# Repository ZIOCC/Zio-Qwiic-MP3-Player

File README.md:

# Zio Qwiic MP3 Player

> This product can be available for purchase [here](https://www.smart-prototyping.com/Zio-Qwiic-MP3-Player).

#### Description

Usually, it is hard to embed sounds into a DIY project, but now we are making it much simpler, the Qwiic version Mp3 player can be very easy to set up and controlled by only writing few lines of commands. No soldering and confusing cable connecting difficulty, only tinkering fun-ness!

Just store the sound files in an Mp3 format to your SD card, plug it into the SD card slot on the module’s backside, and connect a headset/loudspeaker to the 3.5mm audio jack/terminal connector, and you are good to go!

The micro USB connector can connect to your PC and this module can turn into a micro SD card reader, which can be very useful and convenient.

##### How to play soundtracks:

To fully utilized our module, the most useful way is by using code to control everything, including which mp3 file to play, adjusting the volume, equalization, and stereo output.

Or for those of you who are lacking in the programming section, you can opt for the lazy way - give the trigger pins low input, then it will play the corresponding files, like pin #1 will play T001.mp3 file, and pin #3 will play T003.mp3 file, just like that. 

#### Specification

* Operation Voltage: 3.3V
* MP3 IC: WT2003S
* 32 levels volume controlled by code
* Supported SD Card memory: up to 32GB
* Supported File System: FAT16 and FAT32 (Doesn’t Support NTFS)
* Supported audio format: .mp3, .wav
* 3.5mm audio headphone jack
* I2C default address 0x37, can be changed by soldering jumper (the ADDR on the backside)
* I2C gateway MCU: ATTINY84A-SSU
* Dimensions: 45.9x 35.5mm
* Weight: 8.2g

#### Links

* [PCB source file and Gerber file](https://github.com/ZIOCC/Zio-Qwiic-MP3-Player)
* [Schematic](https://github.com/ZIOCC/Zio-Qwiic-MP3-Player/blob/master/Zio%20Qwiic%20MP3%20Player%20Schematic%20PDF.pdf)
* [WT2003S datasheet](https://www.smart-prototyping.com/image/data/NOA-RnD/101942%20MP3%20Player/WT2003S-16S_Chip_V1.03.pdf)
* [Demo code](https://github.com/ZIOCC/Zio-Qwiic-MP3-Player/tree/master/firmware)
* [I2C gateway firmware](https://github.com/ZIOCC/Zio-Qwiic-MP3-Player/tree/master/Gateway_MCU_Firmware)

###### About Zio
> Zio is a new line of open sourced, compact, and grid layout boards, fully integrated for Arduino and Qwiic ecosystem. Designed ideally for wearables, robotics, small-space limitations or other on the go projects. Check out other awesome Zio products [here](https://www.smart-prototyping.com/Zio).

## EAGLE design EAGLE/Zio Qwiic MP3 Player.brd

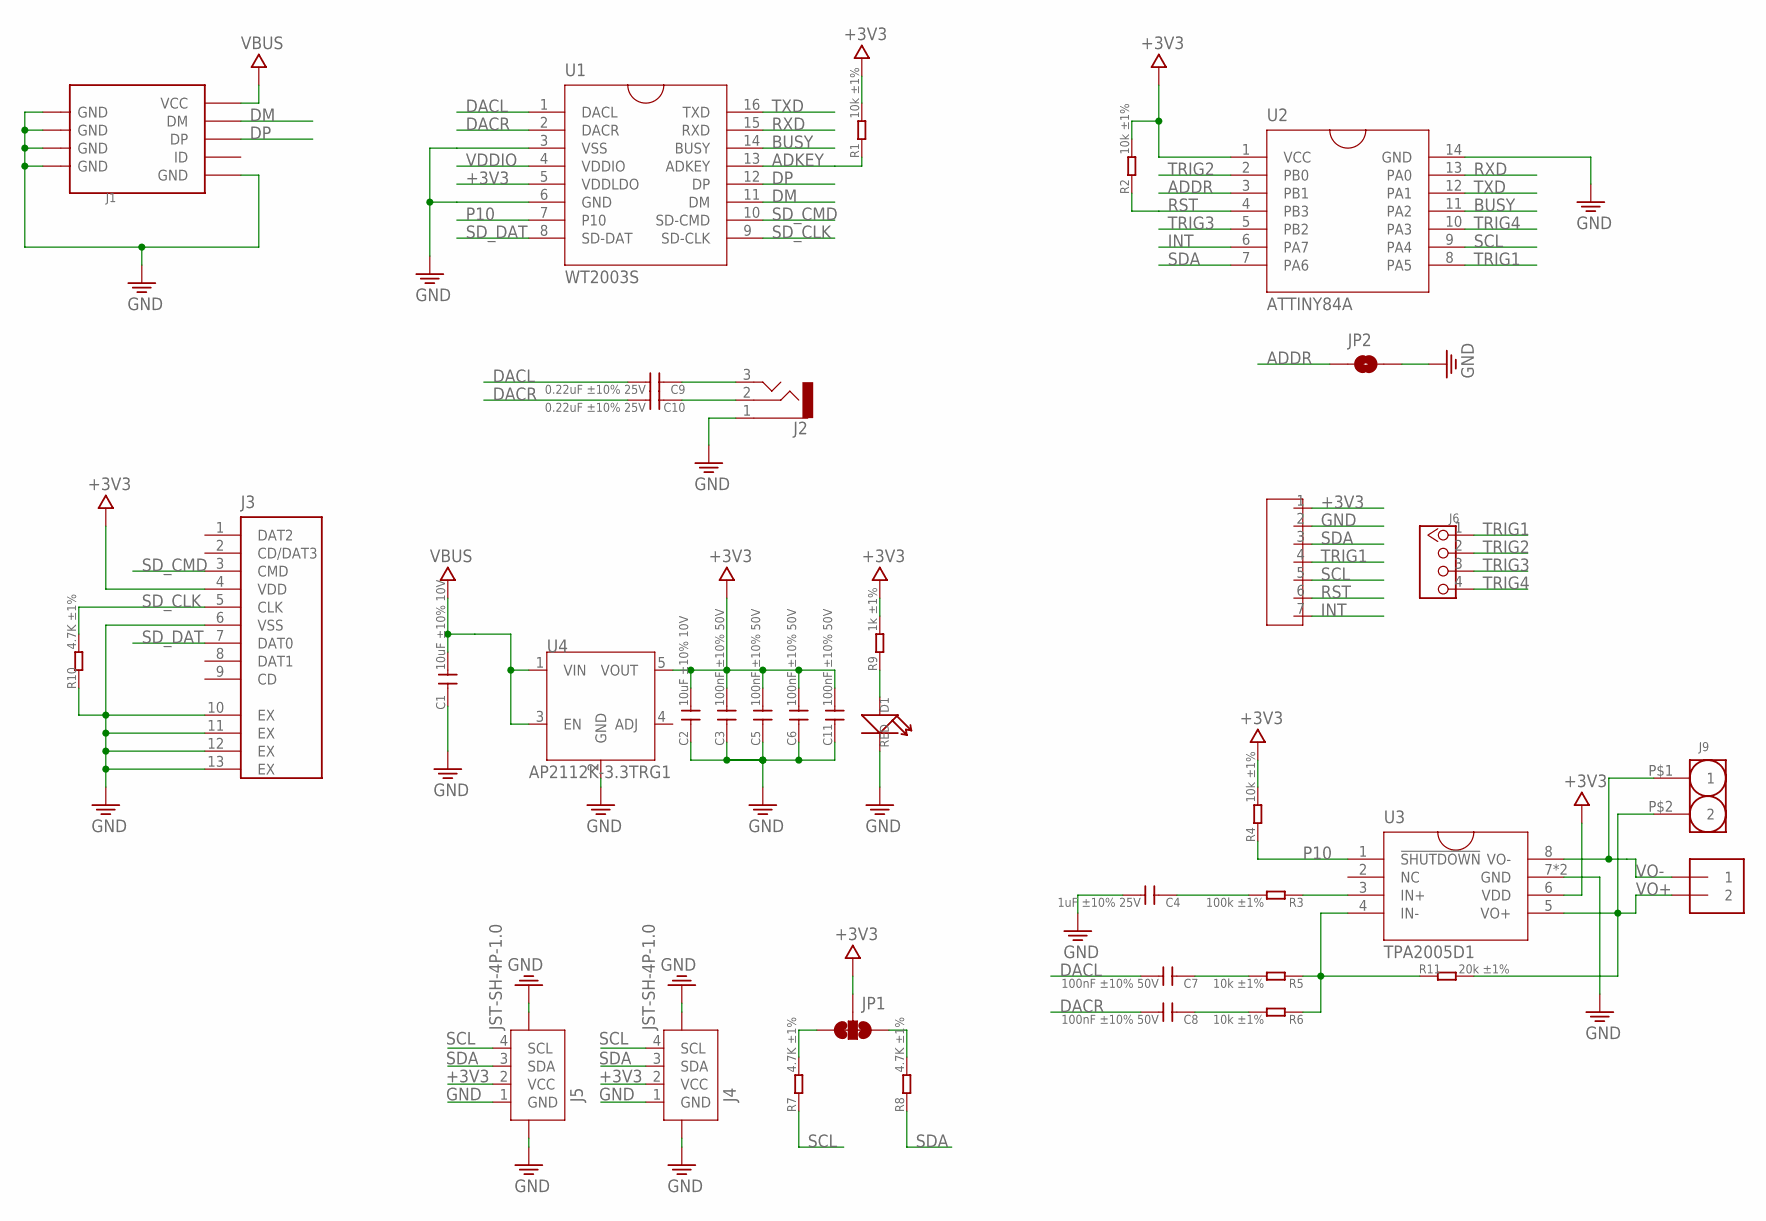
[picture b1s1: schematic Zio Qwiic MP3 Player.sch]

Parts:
C1, C2: 10uF ±10% 10V; C0603
C3, C5, C6, C7, C8, C11: 100nF ±10% 50V; C0603
C4: 1uF ±10% 25V; C0603
C9, C10: 0.22uF ±10% 25V; C0603
D1: RED; LED-0603
J1: USB-MICROE; MICRO-SMD
J2: AUDIO-3PPJ-320B; 3P-SMD-3.5MM
J3: TF_CARD
J4, J5: JST-SH-4P-1.0; JST-SH-4P
J6: HEADER-4P-60/35MIL; 4P-65/35MIL
J7: HEADER-7P; 7P-2.54-60/35MIL
J8: TERMBLOCK_1X2-3.5MM; 1X2-3.5MM
J9: HEADER-2P; 插片
JP1: SMT-JUMPER_3_2-NC_TRACE
JP2: JUMPER-SMT_2_NC_PASTE_NOCREM; SMT-JUMPER_2_NC_PASTE_SILK_NOCREM
R1, R2, R4, R5, R6: 10k ±1%; R0603
R3: 100k ±1%; R0603
R7, R8, R10: 4.7K ±1%; R0603
R9: 1k ±1%; R0603
R11: 20k ±1%; R0603
U1: WT2003S; SO16
U2: ATTINY84A; SO14
U3: TPA2005D1; MSOP-8
U4: AP2112K-3.3TRG1; SOT23-5

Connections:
+3V3: C2.2, C3.2, C5.2, C6.2, C11.2, J3.4 (VDD), J4.2 (VCC), J5.2 (VCC), J7.1, JP1.2, R1.2, R2.2, R4.2, R9.2, U1.5 (VDDLDO), U2.1 (VCC), U3.6 (VDD), U4.5 (VOUT)
ADDR: JP2.1, U2.3 (PB1)
ADKEY: R1.1, U1.13 (ADKEY)
BUSY: U1.14 (BUSY), U2.11 (PA2)
DACL: C7.2, C9.2, U1.1 (DACL)
DACR: C8.2, C10.2, U1.2 (DACR)
DM: J1.D- (DM), U1.11 (DM)
DP: J1.D+ (DP), U1.12 (DP)
GND: C1.1, C2.1, C3.1, C4.2, C5.1, C6.1, C11.1, D1.-, J1.GND, J1.S1 (GND), J1.S1@1 (GND), J1.S1@2 (GND), J1.S2 (GND), J1.S2@1 (GND), J1.S2@2 (GND), J1.S3 (GND), J1.S3@1 (GND), J1.S3@2 (GND), J1.S4 (GND), J1.S4@1 (GND), J1.S4@2 (GND), J1.S5 (GND), J1.S6 (GND), J2.1, J3.6 (VSS), J3.10 (EX), J3.11 (EX), J3.12 (EX), J3.13 (EX), J4.1 (GND), J4.NC1 (5), J4.NC2 (6), J5.1 (GND), J5.NC1 (5), J5.NC2 (6), J7.2, JP2.2, R10.1, U1.3 (VSS), U1.6 (GND), U2.14 (GND), U3.7 (GND), U3.9 (GND), U4.2 (GND)
INT: J7.7, U2.6 (PA7)
unnamed: D1.+, R9.1
unnamed: C4.1, R3.2
unnamed: R3.1, U3.3 (IN+)
unnamed: R5.1, R6.1, R11.1, U3.4 (IN-)
unnamed: C9.1, J2.3
unnamed: C10.1, J2.2
unnamed: C8.1, R6.2
unnamed: C7.1, R5.2
unnamed: JP1.3, R7.2
unnamed: JP1.1, R8.2
P10: R4.1, U1.7 (P10), U3.1 (!SHUTDOWN)
RST: J7.6, R2.1, U2.4 (PB3)
RXD: U1.15 (RXD), U2.13 (PA0)
SCL: J4.4 (SCL), J5.4 (SCL), J7.5, R7.1, U2.9 (PA4)
SDA: J4.3 (SDA), J5.3 (SDA), J7.3, R8.1, U2.7 (PA6)
SD_CLK: J3.5 (CLK), R10.2, U1.9 (SD-CLK)
SD_CMD: J3.3 (CMD), U1.10 (SD-CMD)
SD_DAT: J3.7 (DAT0), U1.8 (SD-DAT)
TRIG1: J6.1, J7.4, U2.8 (PA5)
TRIG2: J6.2, U2.2 (PB0)
TRIG3: J6.3, U2.5 (PB2)
TRIG4: J6.4, U2.10 (PA3)
TXD: U1.16 (TXD), U2.12 (PA1)
VBUS: C1.2, J1.VBUS (VCC), U4.1 (VIN), U4.3 (EN)
VDDIO: U1.4 (VDDIO)
VO+: J8.2, J9.P$2 (2), R11.2, U3.5 (VO+)
VO-: J8.1, J9.P$1 (1), U3.8 (VO-)

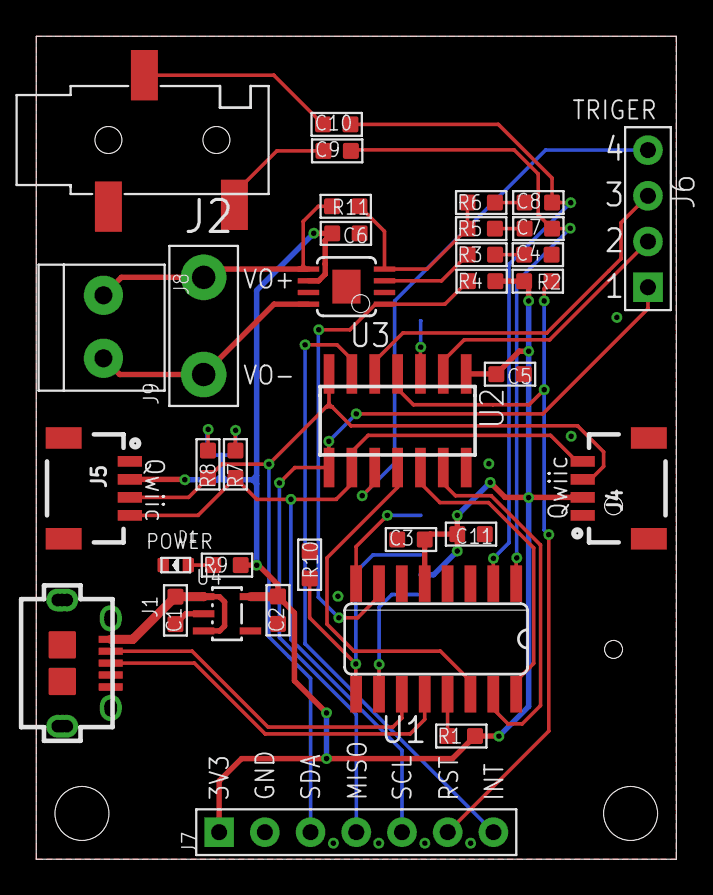
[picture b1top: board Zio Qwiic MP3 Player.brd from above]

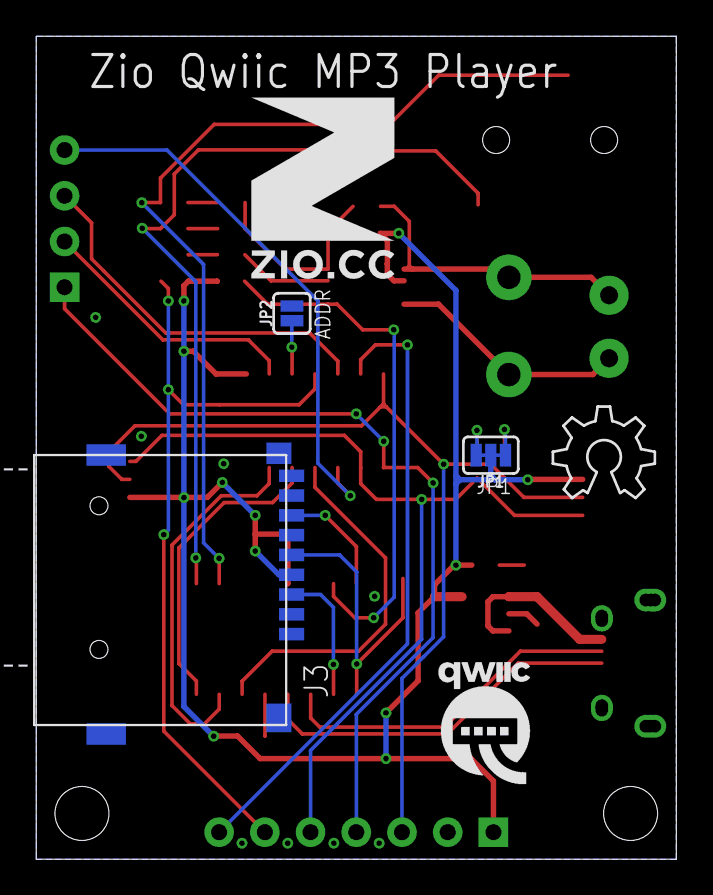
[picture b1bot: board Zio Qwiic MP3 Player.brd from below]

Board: 2 copper layers, 35.6 x 45.7 mm, 41 parts (6 on the bottom side), 36 nets.

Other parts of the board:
U$11: 10MM
U$12: QWIIC-LOGO-MEDIUM
U$13: OSHW_6X200_NOTEXT
